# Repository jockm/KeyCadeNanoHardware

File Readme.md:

KeyCade Nano Hardware
=====================

Hardware files for the [KeyCade Nano](https://github.com/jockm/KeyCadeNano) project.  

This will include:

* EDA (Eagle CAD) files for the KeyCade Nano
* Bill of Materials
* Notes
* Etc

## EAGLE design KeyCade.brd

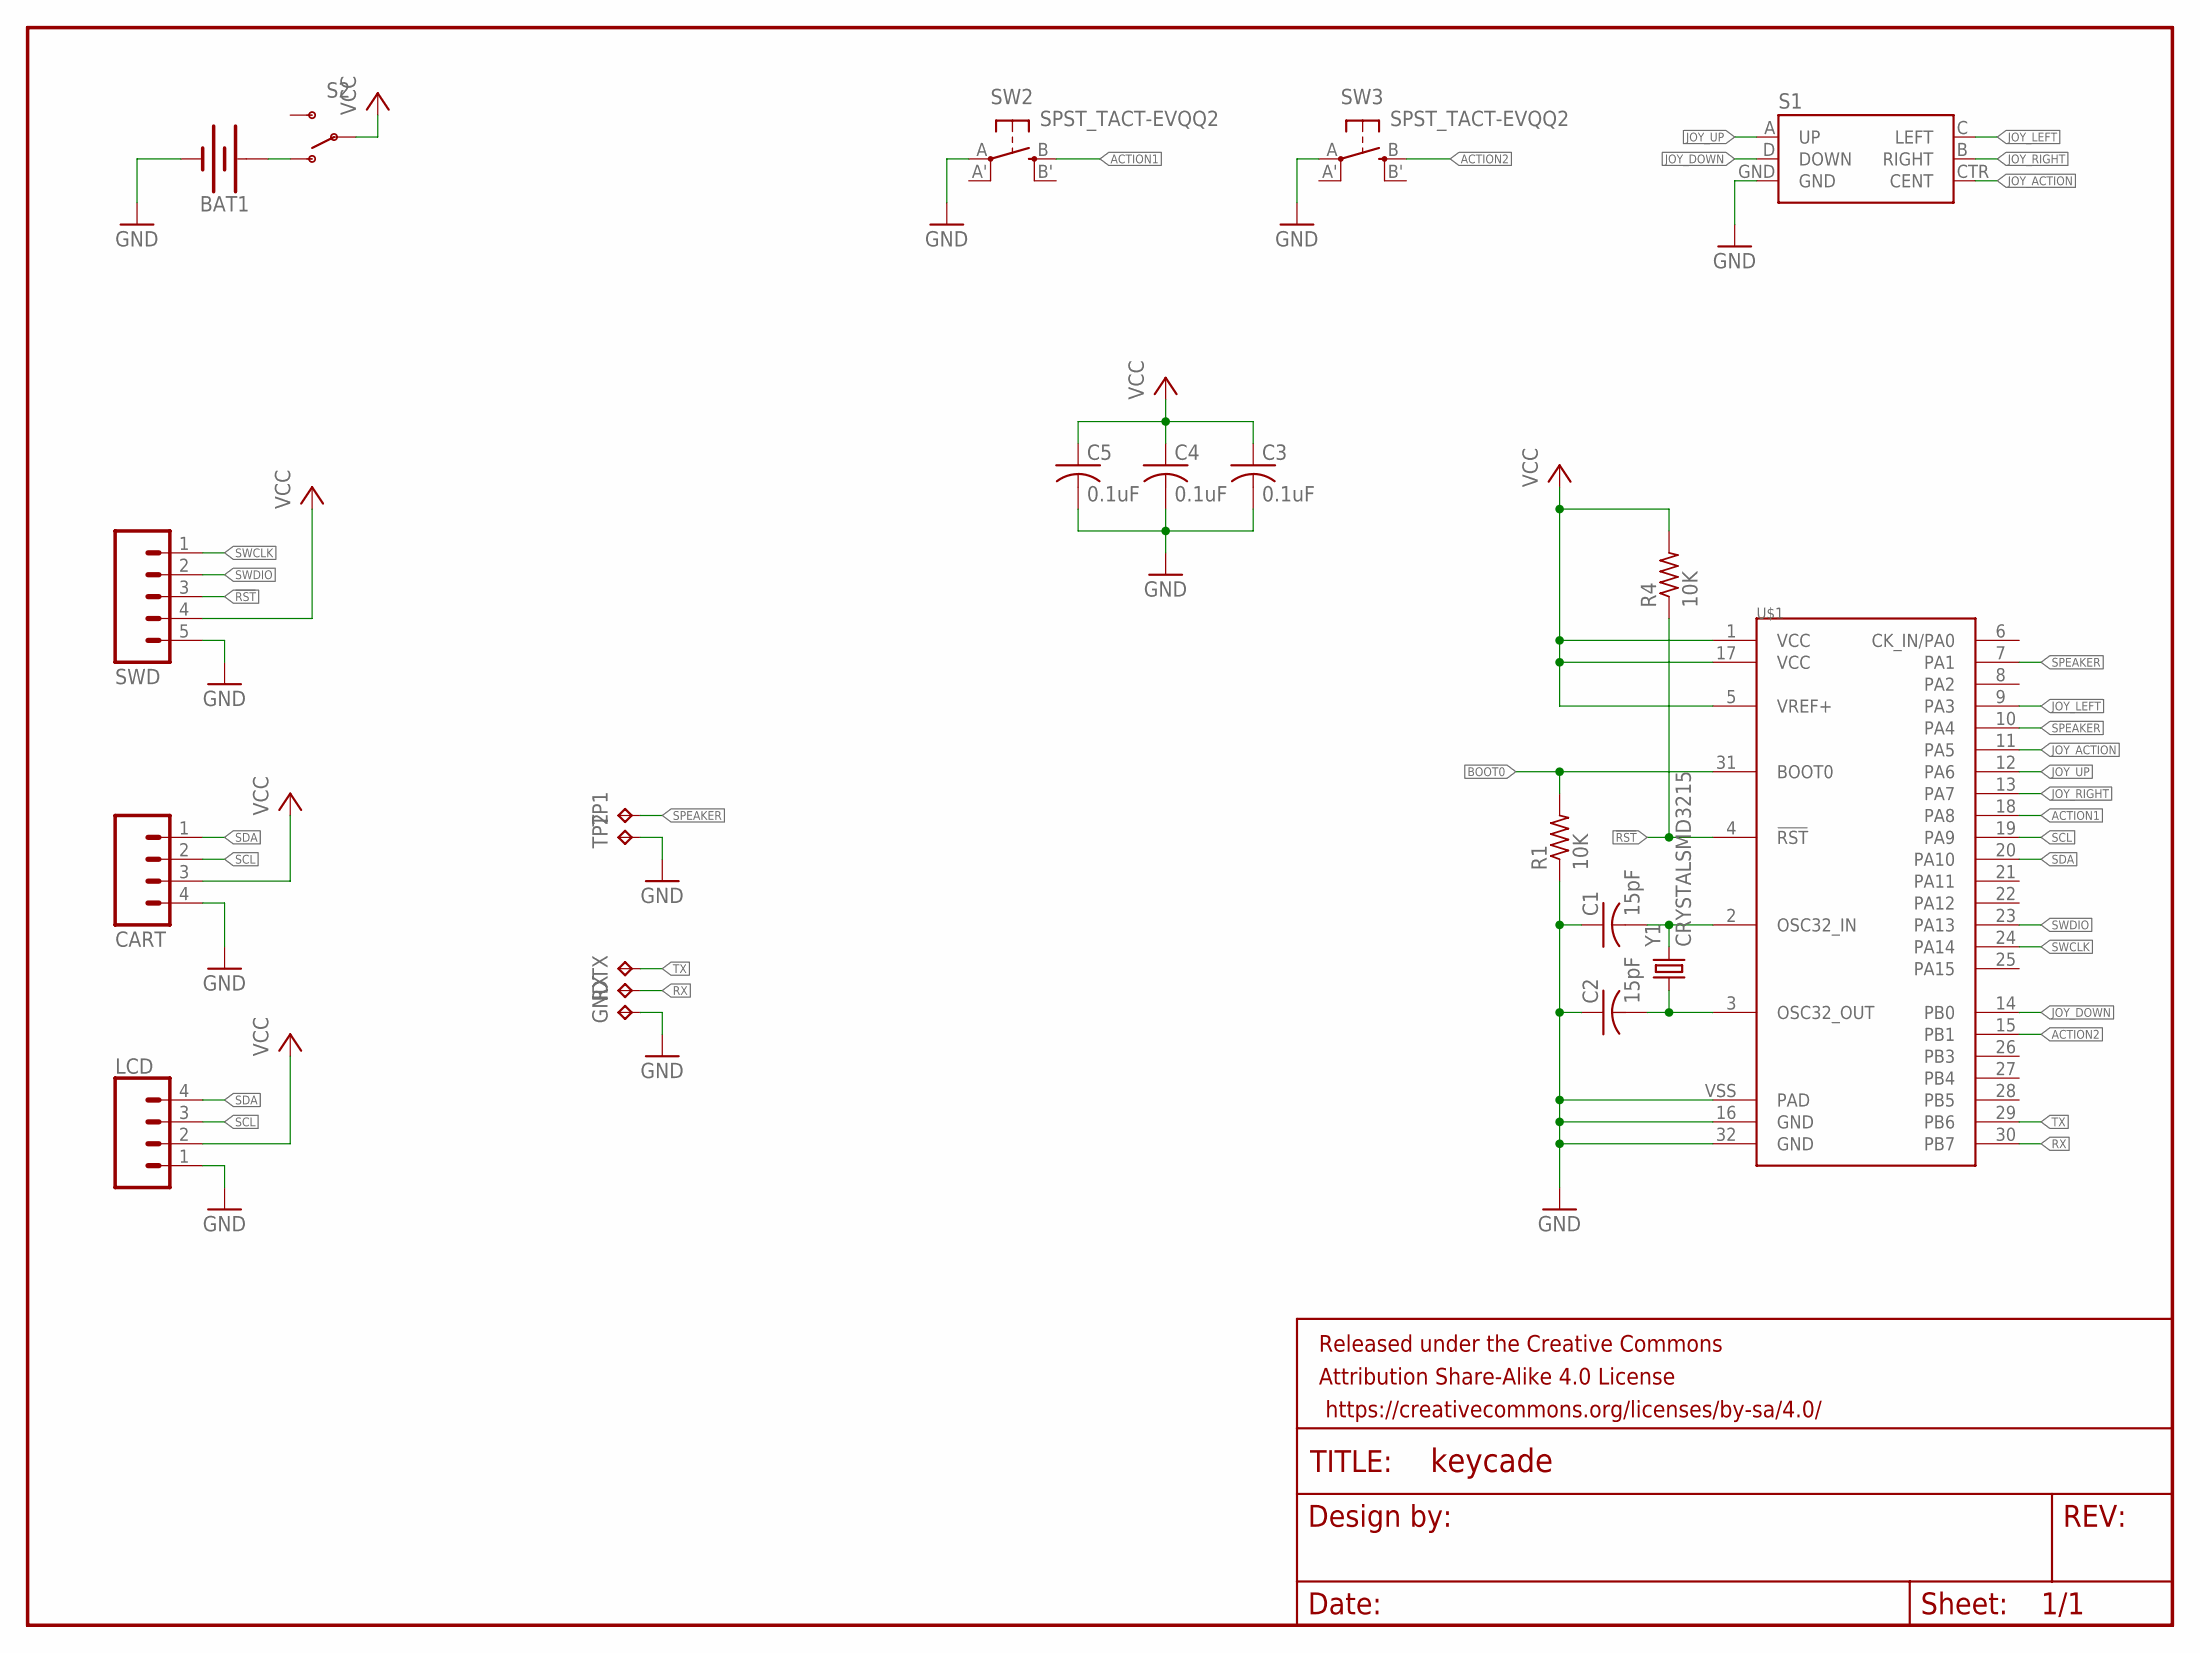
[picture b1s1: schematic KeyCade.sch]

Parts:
BAT1: BATTERY-20MM_SMD_4LEGS; BATTCON_20MM_4LEGS
C1, C2: 15pF; C0603
C3, C4, C5: 0.1uF; C0603
CART: M04PTH; 1X04@1
FRAME1: FRAME-LETTER; CREATIVE_COMMONS
GND: TPTP17SQ; TP17SQ
LCD: CONN_04SMD_RA_FEMALE; 1X04_SMD_RA_FEMALE
R1, R4: 10K; R0603
RX: TPTP17SQ; TP17SQ
S1: JOYSTICK_MINI
S2: SWITCH-SPDT-SMD-A; SWITCH-SPST-SMD-A
SW2, SW3: SPST_TACT-EVQQ2; EVQ-Q2
SWD: M05PTH; 1X05
TP1, TP2: TPTP17SQ; TP17SQ
TX: TPTP17SQ; TP17SQ
U$1: STM32L432KCIC; UFQFPN32
Y1: CRYSTALSMD3215; ST3215SB_32X15

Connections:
!RST: R4.1, SWD.3, U$1.4 (!RST)
+3V: BAT1.POSITIVE@1 (+), BAT1.POSITIVE@2 (+), BAT1.POSITIVE@3 (+), BAT1.POSITIVE@4 (+), S2.1 (O)
ACTION1: SW2.B (S), U$1.18 (PA8)
ACTION2: SW3.B (S), U$1.15 (PB1)
BOOT0: R1.2, U$1.31 (BOOT0)
GND: BAT1.NEGATIVE (-), C1.1, C2.1, C3.2, C4.2, C5.2, CART.4, GND.TP, LCD.1, R1.1, S1.GND, SW2.A, SW3.A, SWD.5, TP2.TP, U$1.16 (GND), U$1.32 (GND), U$1.VSS (PAD)
JOY_ACTION: S1.CTR (CENT), U$1.11 (PA5)
JOY_DOWN: S1.D (DOWN), U$1.14 (PB0)
JOY_LEFT: S1.C (LEFT), U$1.9 (PA3)
JOY_RIGHT: S1.B (RIGHT), U$1.13 (PA7)
JOY_UP: S1.A (UP), U$1.12 (PA6)
OSC32_IN: C1.2, U$1.2 (OSC32_IN), Y1.2
OSC32_OUT: C2.2, U$1.3 (OSC32_OUT), Y1.1
RX: RX.TP, U$1.30 (PB7)
SCL: CART.2, LCD.3, U$1.19 (PA9)
SDA: CART.1, LCD.4, U$1.20 (PA10)
SPEAKER: TP1.TP, U$1.7 (PA1), U$1.10 (PA4)
SWCLK: SWD.1, U$1.24 (PA14)
SWDIO: SWD.2, U$1.23 (PA13)
TX: TX.TP, U$1.29 (PB6)
VCC: C3.1, C4.1, C5.1, CART.3, LCD.2, R4.2, S2.2, SWD.4, U$1.1 (VCC), U$1.5 (VREF+), U$1.17 (VCC)

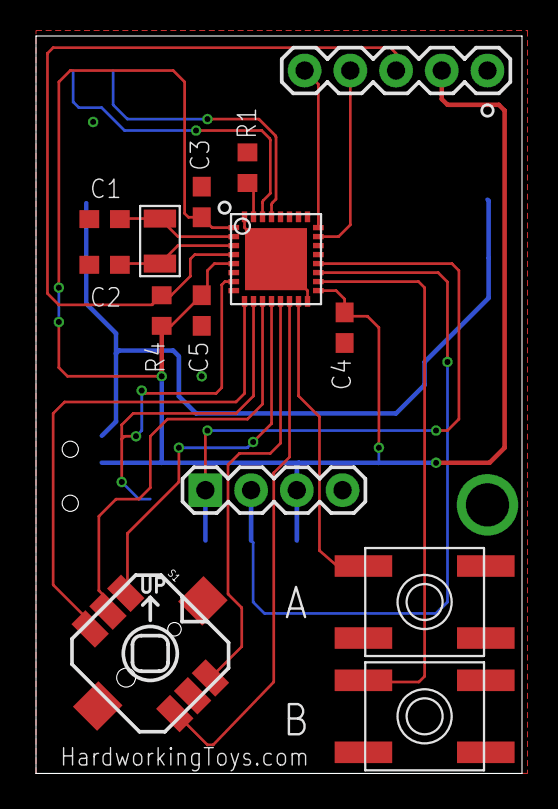
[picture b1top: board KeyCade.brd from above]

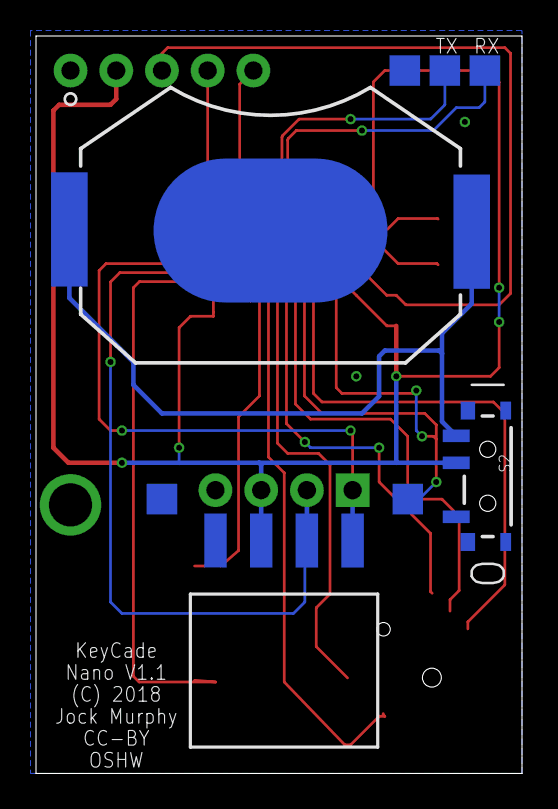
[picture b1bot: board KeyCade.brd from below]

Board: 2 copper layers, 27.0 x 41.0 mm, 23 parts (8 on the bottom side), 21 nets.

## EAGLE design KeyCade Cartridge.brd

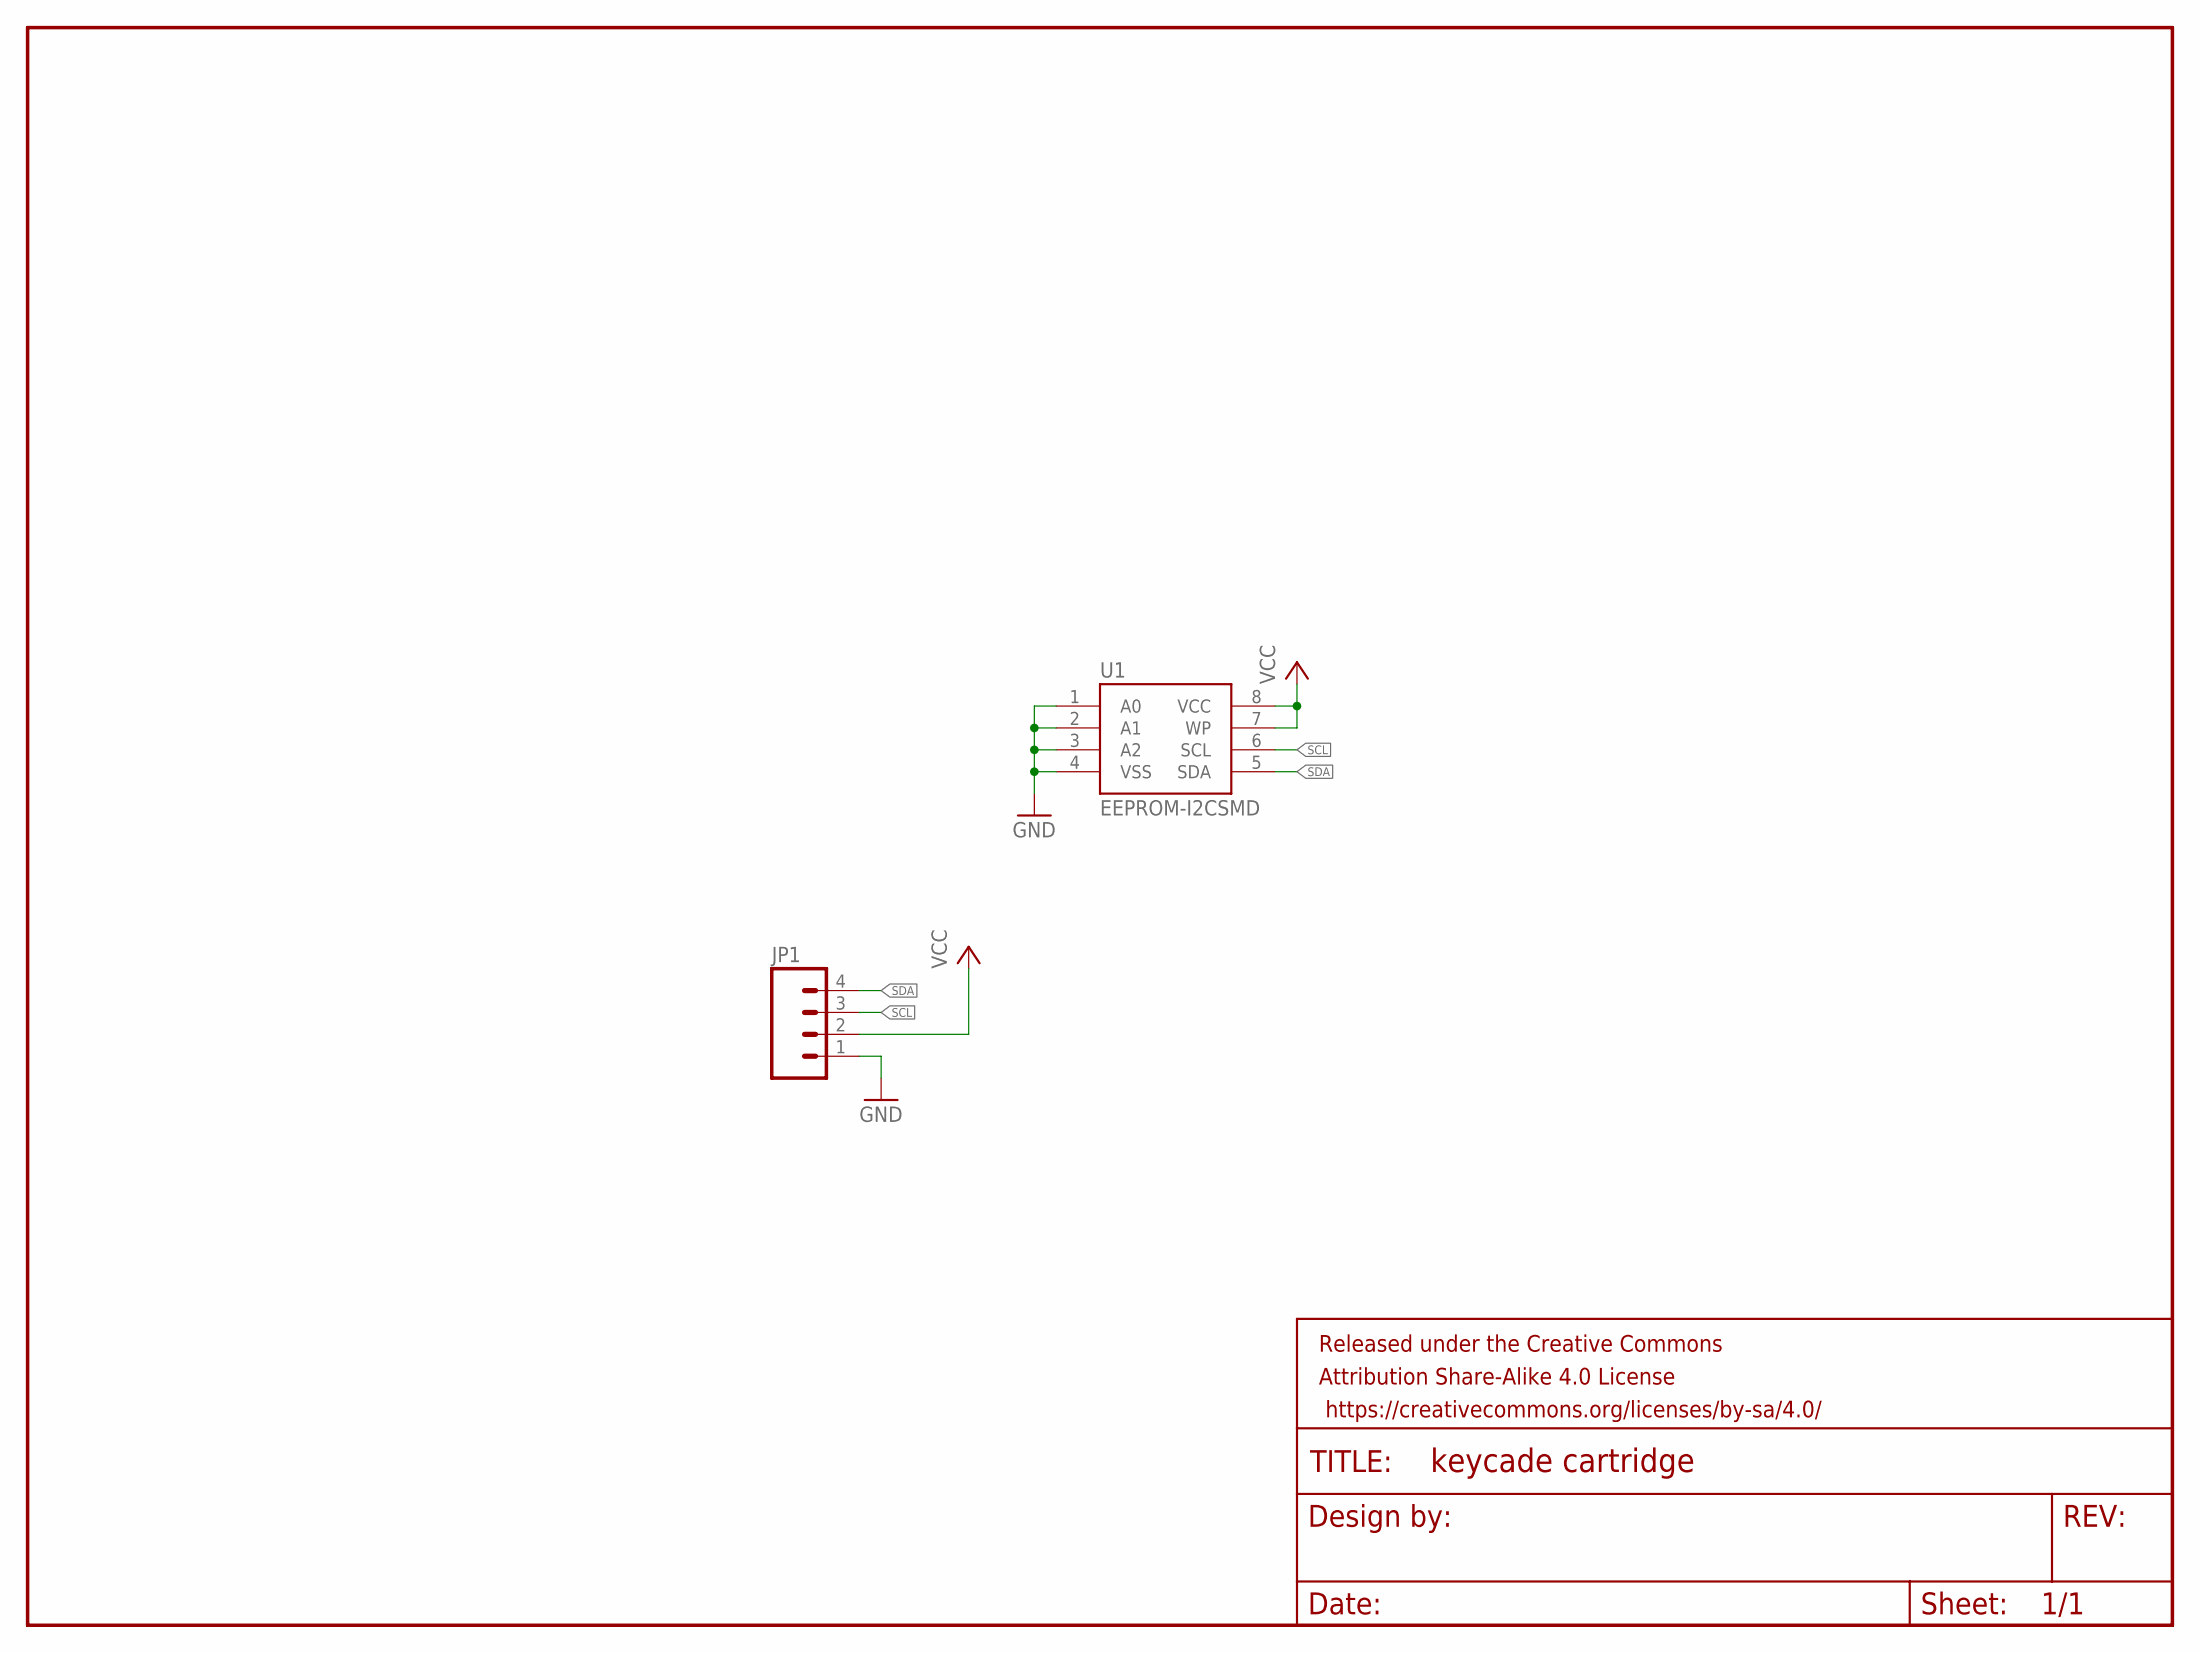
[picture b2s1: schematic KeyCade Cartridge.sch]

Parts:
FRAME1: FRAME-LETTER; CREATIVE_COMMONS
JP1: M04PTH; 1X04
U1: EEPROM-I2CSMD; SO08

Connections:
GND: JP1.1, U1.1 (A0), U1.2 (A1), U1.3 (A2), U1.4 (VSS)
SCL: JP1.3, U1.6 (SCL)
SDA: JP1.4, U1.5 (SDA)
VCC: JP1.2, U1.7 (WP), U1.8 (VCC)

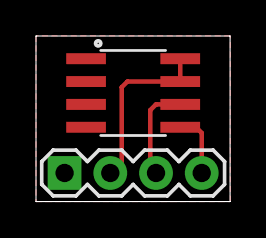
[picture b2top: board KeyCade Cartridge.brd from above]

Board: 2 copper layers, 10.8 x 9.2 mm, 3 parts (0 on the bottom side), 4 nets.

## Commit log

2018-02-10 Initial Checkin
2018-02-10 Fleshed out (a little)
2018-02-14 Aestheric updates
    Initial Checkin
2018-02-14 Removed so better named replacement could be used

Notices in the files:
KeyCade.brd:
(C) 2018
CC-BY
parts and their libraries:
SparkFun-Connectors: Licensing: Creative Commons ShareAlike 4.0 International - https://creativecommons.org/licenses/by-sa/4.0
StuffLabs: Released under the Creative Commons Attribution 4.0 License
StuffLabs: https://creativecommons.org/licenses/by/4.0
StuffLabs: Released under the Creative Commons
